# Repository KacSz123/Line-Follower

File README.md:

# Line-Follower
Project of Line Follower based on ATmega328p and CNY70.

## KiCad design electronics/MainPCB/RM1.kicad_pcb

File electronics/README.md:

# Electronics
Description, schematics and PCB

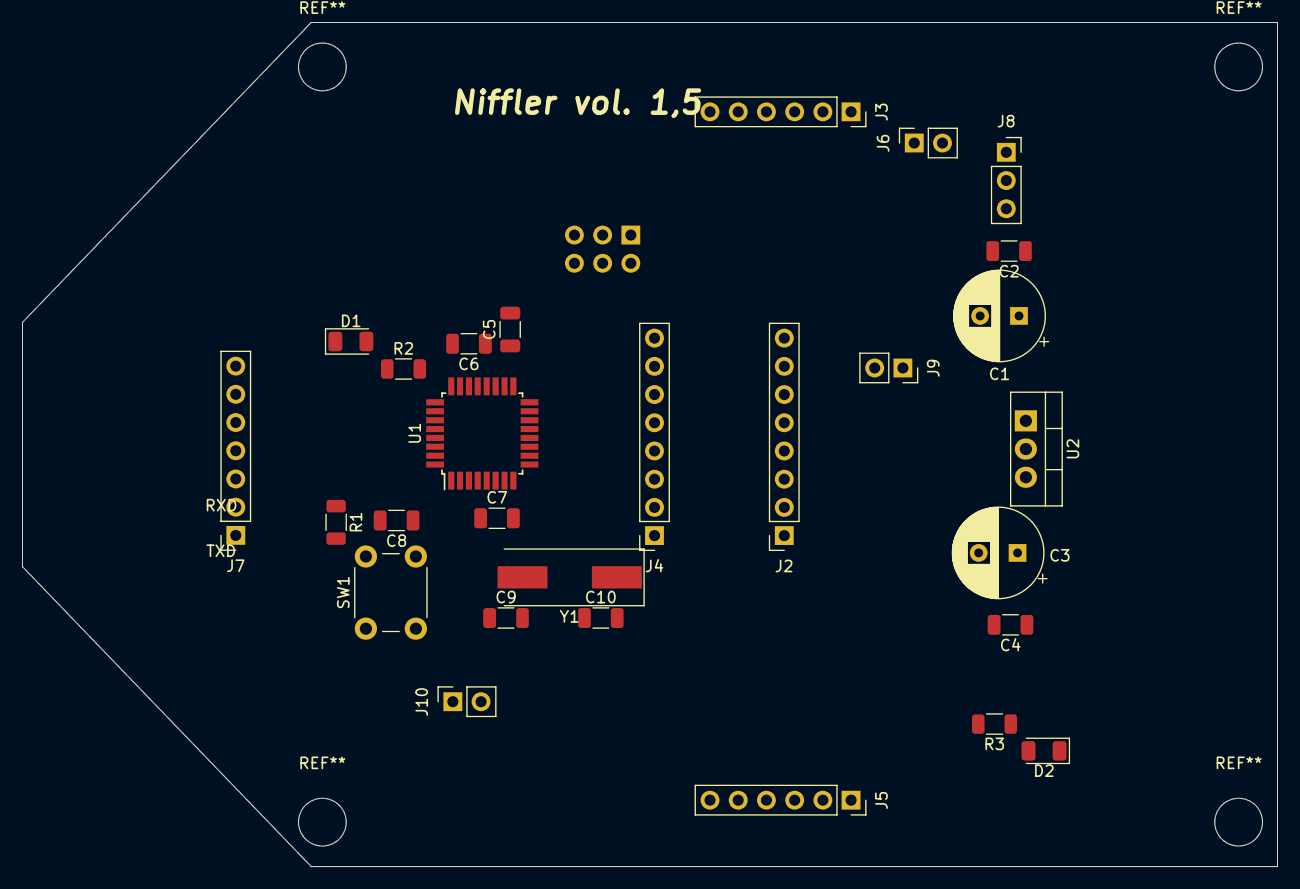
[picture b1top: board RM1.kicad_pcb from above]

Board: 2 copper layers, 113.0 x 76.0 mm, 29 parts (1 on the bottom side), 35 nets, no tracks yet.

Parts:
C1: 470u; CP_Radial_D8.0mm_P3.50mm
C2, C4, C5, C6, C7, C8: 100n; C_1206_3216Metric
C3: 100u; CP_Radial_D8.0mm_P3.50mm
C9, C10: C; C_1206_3216Metric
D1, D2: LED; LED_1206_3216Metric
J1: AVR-ISP-6; PinSocket_2x03_P2.54mm_Vertical
J2, J4: Conn_01x08; PinSocket_1x08_P2.54mm_Vertical
J3, J5: Conn_01x06; PinSocket_1x06_P2.54mm_Vertical
J6, J9, J10: Conn_01x02; PinSocket_1x02_P2.54mm_Vertical
J7: Conn_01x07; PinSocket_1x07_P2.54mm_Vertical
J8: Conn_01x03; PinSocket_1x03_P2.54mm_Vertical
R1, R2, R3: 10k; R_1206_3216Metric
SW1: SW_SPST; SW_PUSH_6mm_H5mm
U1: ATmega328P-PU; TQFP-32_7x7mm_P0.8mm
U2: L7805; TO-220-3_Vertical
Y1: 16Mhz; Crystal_SMD_HC49-SD

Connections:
5V: C3.1, C4.1, C5.1, C7.1, J1.2 (VCC), J2.2, J3.3, J4.4, J5.3, J7.1, R1.1, R3.2, U1.7 (VCC), U1.20 (AVCC), U2.3 (VO)
6V: J2.7, J9.2
AIN1: J4.3, U1.15 (PB1)
AIN2: J4.2, U1.14 (PB0)
AO1: J2.6, J3.1
AO2: J2.5, J3.2
AREF: C6.1, U1.21 (AREF)
BIN1: J4.5, U1.16 (PB2)
BO1: J2.3, J5.1
BO2: J2.4, J5.2
GND: C1.2, C2.2, C3.2, C4.2, C5.2, C6.2, C7.2, C8.1, C9.1, C10.1, D1.1 (K), D2.1 (K), J1.6 (GND), J2.1, J2.8, J3.6, J4.8, J5.6, J6.1, J7.7, SW1.2 (B), U1.8 (GND), U1.22 (GND), U2.2 (GND)
MISO\PB4: J1.1 (MISO), U1.18 (PB4)
MOSI\PB3: J1.4 (MOSI), J4.6, U1.17 (PB3)
unnamed: C1.1, C2.1, J8.3, J9.1, U2.1 (VI)
unnamed: C9.2, U1.9 (XTAL1/PB6), Y1.2
unnamed: C10.2, U1.10 (XTAL2/PB7), Y1.1
unnamed: D1.2 (A), R2.1
unnamed: D2.2 (A), R3.1
unnamed: J6.2, J8.1, J8.2
unnamed: J10.1, U1.2 (PD0)
unnamed: J10.2, U1.3 (PD1)
OUT1A: J3.4, U1.13 (PD7)
OUT1B: J3.5, U1.12 (PD6)
OUT2A: J5.4, U1.4 (PD2)
OUT2B: J5.5, U1.6 (PD4)
PC0: R2.2, U1.23 (PC0)
PC1: J7.6, U1.24 (PC1)
PC2: J7.5, U1.25 (PC2)
PC3: J7.4, U1.26 (PC3)
PC4: J7.3, U1.27 (PC4)
PC5: J7.2, U1.28 (PC5)
PC6\RST: C8.2, J1.5 (~RST), R1.2, SW1.1 (A), U1.1 (~RESET/PC6)
PWMA: J4.1, U1.5 (PD3)
PWMB: J4.7, U1.11 (PD5)
sck\PB5: J1.3 (SCK), U1.19 (PB5)

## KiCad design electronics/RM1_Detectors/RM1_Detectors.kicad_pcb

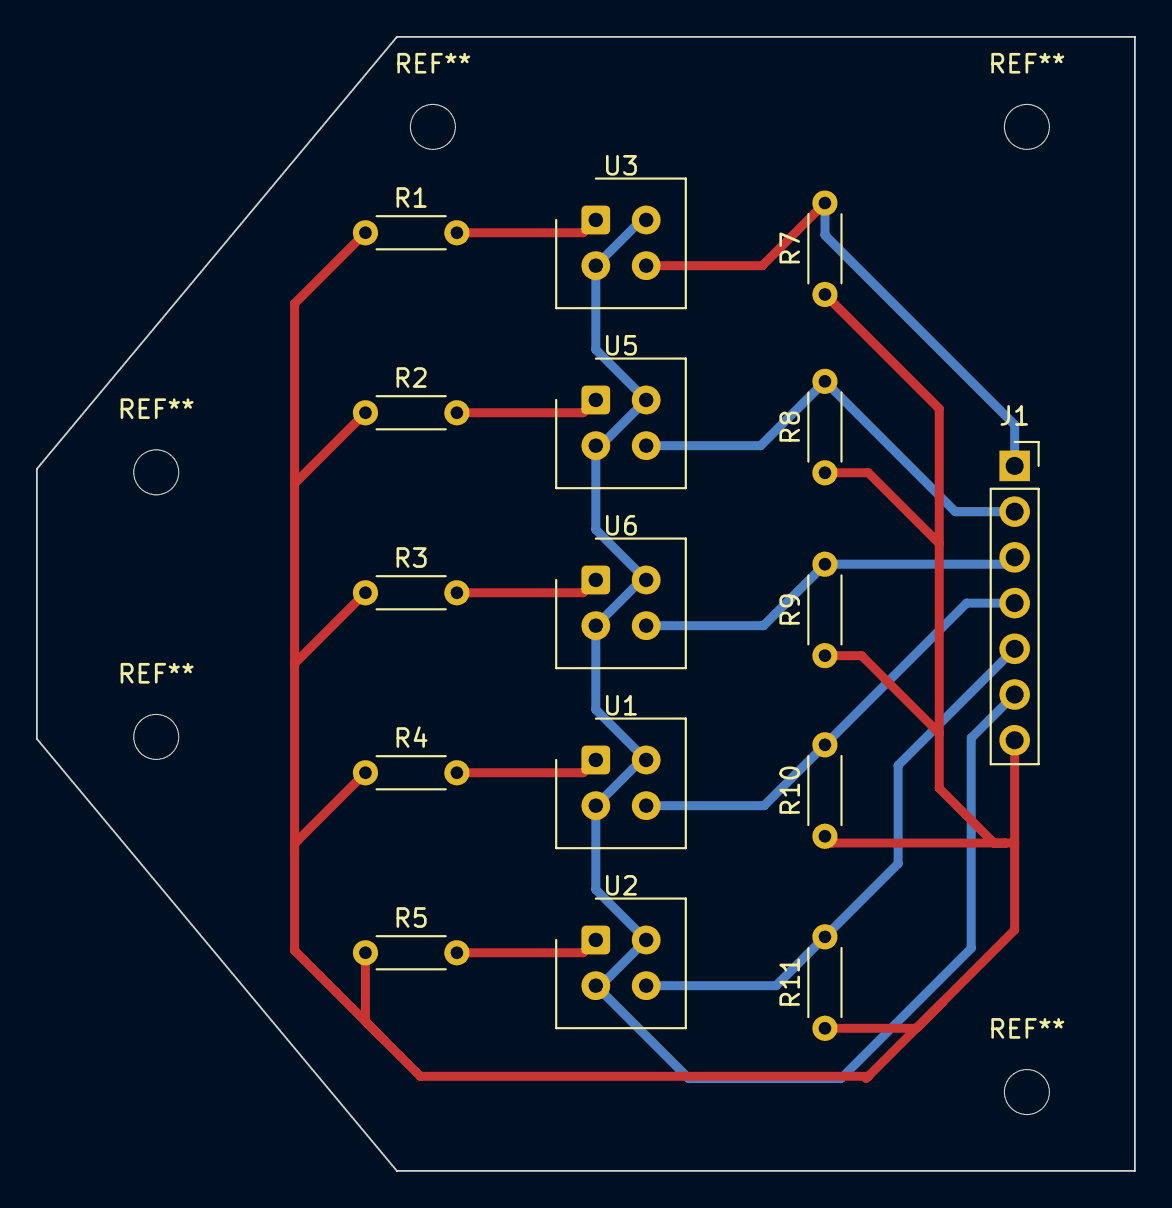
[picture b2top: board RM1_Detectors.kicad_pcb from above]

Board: 2 copper layers, 61.0 x 63.0 mm, 16 parts (0 on the bottom side), 12 nets.

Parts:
J1: Conn_01x07; PinSocket_1x07_P2.54mm_Vertical
R1, R2, R3, R4, R5: 200; R_Axial_DIN0204_L3.6mm_D1.6mm_P5.08mm_Horizontal
R7, R8, R9, R10, R11: 10k; R_Axial_DIN0204_L3.6mm_D1.6mm_P5.08mm_Horizontal
U1, U2, U3, U5, U6: CNY70; Vishay_CNY70

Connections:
5V: J1.7, R1.1, R2.1, R3.1, R4.1, R5.1, R7.1, R8.1, R9.1, R10.1, R11.1
GND: J1.6, U1.2, U1.4, U2.2, U2.4, U3.2, U3.4, U5.2, U5.4, U6.2, U6.4
unnamed: J1.1, R7.2, U3.3
unnamed: J1.2, R8.2, U5.3
unnamed: J1.3, R9.2, U6.3
unnamed: J1.4, R10.2, U1.3
unnamed: J1.5, R11.2, U2.3
unnamed: R1.2, U3.1
unnamed: R2.2, U5.1
unnamed: R3.2, U6.1
unnamed: R4.2, U1.1
unnamed: R5.2, U2.1

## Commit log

2022-05-19 project initiated
2022-05-20 initiated project of electronics in smd
